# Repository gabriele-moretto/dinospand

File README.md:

# DinoSpand

The purpose of this board is to be mounted on a fertilizer spreader (an agricultural tool) to manage the drawer in which we load/unload the fertilizer.
While managing the tool, we'll see all the information in the cabin on the little OLED screen on the board, but also we will able to connect the device to our smartphone in order to managing some settings.

## Hardware

The microcontroller used is an ESP32-s3, which is useful for the right number of GPIO we need and for the bluetooth functions.

## Firmware

## [PCBWay](https://www.pcbway.com/) production
I had a great experience working with **PCBWay** through their sponsorship program. They supported my project by manufacturing and shipping a fully assembled PCB, which allowed me to turn my design into a real, working device.

**Key points:**
- PCB manufacturing
- High-quality fabrication and assembly
- Easy ordering process
- Fast production and shipping
- Reliable results

Many thanks to PCBWay for supporting this project!

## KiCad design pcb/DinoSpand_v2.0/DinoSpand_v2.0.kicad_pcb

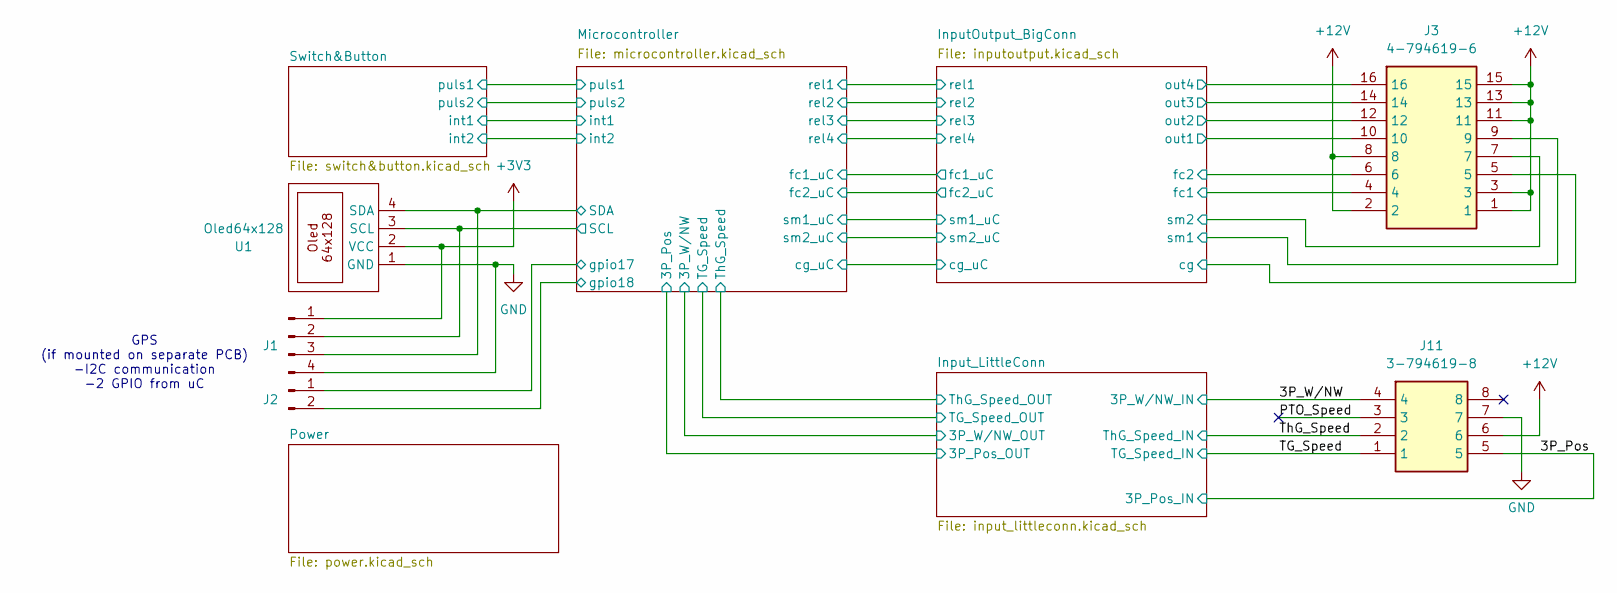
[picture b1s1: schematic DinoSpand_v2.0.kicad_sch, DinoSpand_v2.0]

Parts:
J1: Conn_01x04_Pin; PinHeader_1x04_P2.54mm_Vertical
J2: Conn_01x02_Pin; PinHeader_1x02_P2.54mm_Vertical
J3: 4-794619-6; 47946196; Mouser Part Number 571-4-794619-6
J11: 3-794619-8; 37946198; Mouser Part Number 571-3-794619-8
U1: Oled64x128; 128x64OLED

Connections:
+3V3: J1.1, U1.2 (VCC); also elsewhere on the board
+12V: J3.1, J3.2, J3.3, J3.8, J3.11, J3.13, J3.15, J11.6; also elsewhere on the board
/3P_Pos: J11.5; also elsewhere on the board
/3P_W/NW: J11.4; also elsewhere on the board
/InputOutput_BigConn/cg: J3.5; also elsewhere on the board
/InputOutput_BigConn/out1: J3.10; also elsewhere on the board
/InputOutput_BigConn/out2: J3.12; also elsewhere on the board
/InputOutput_BigConn/out3: J3.14; also elsewhere on the board
/InputOutput_BigConn/out4: J3.16; also elsewhere on the board
/InputOutput_BigConn/sm1: J3.9; also elsewhere on the board
/InputOutput_BigConn/sm2: J3.7; also elsewhere on the board
/Microcontroller/GPIO10: J3.4; also elsewhere on the board
/Microcontroller/GPIO11: J3.6; also elsewhere on the board
/Microcontroller/GPIO15: J1.3, U1.4 (SDA); also elsewhere on the board
/Microcontroller/GPIO16: J1.2, U1.3 (SCL); also elsewhere on the board
/Microcontroller/GPIO17: J2.1; also elsewhere on the board
/Microcontroller/GPIO18: J2.2; also elsewhere on the board
/PTO_Speed: J11.3
/TG_Speed: J11.1; also elsewhere on the board
/ThG_Speed: J11.2; also elsewhere on the board
GND: J1.4, J11.7, U1.1 (GND); also elsewhere on the board

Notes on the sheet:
GPS (if mounted on separate PCB) -I2C communication -2 GPIO from uC

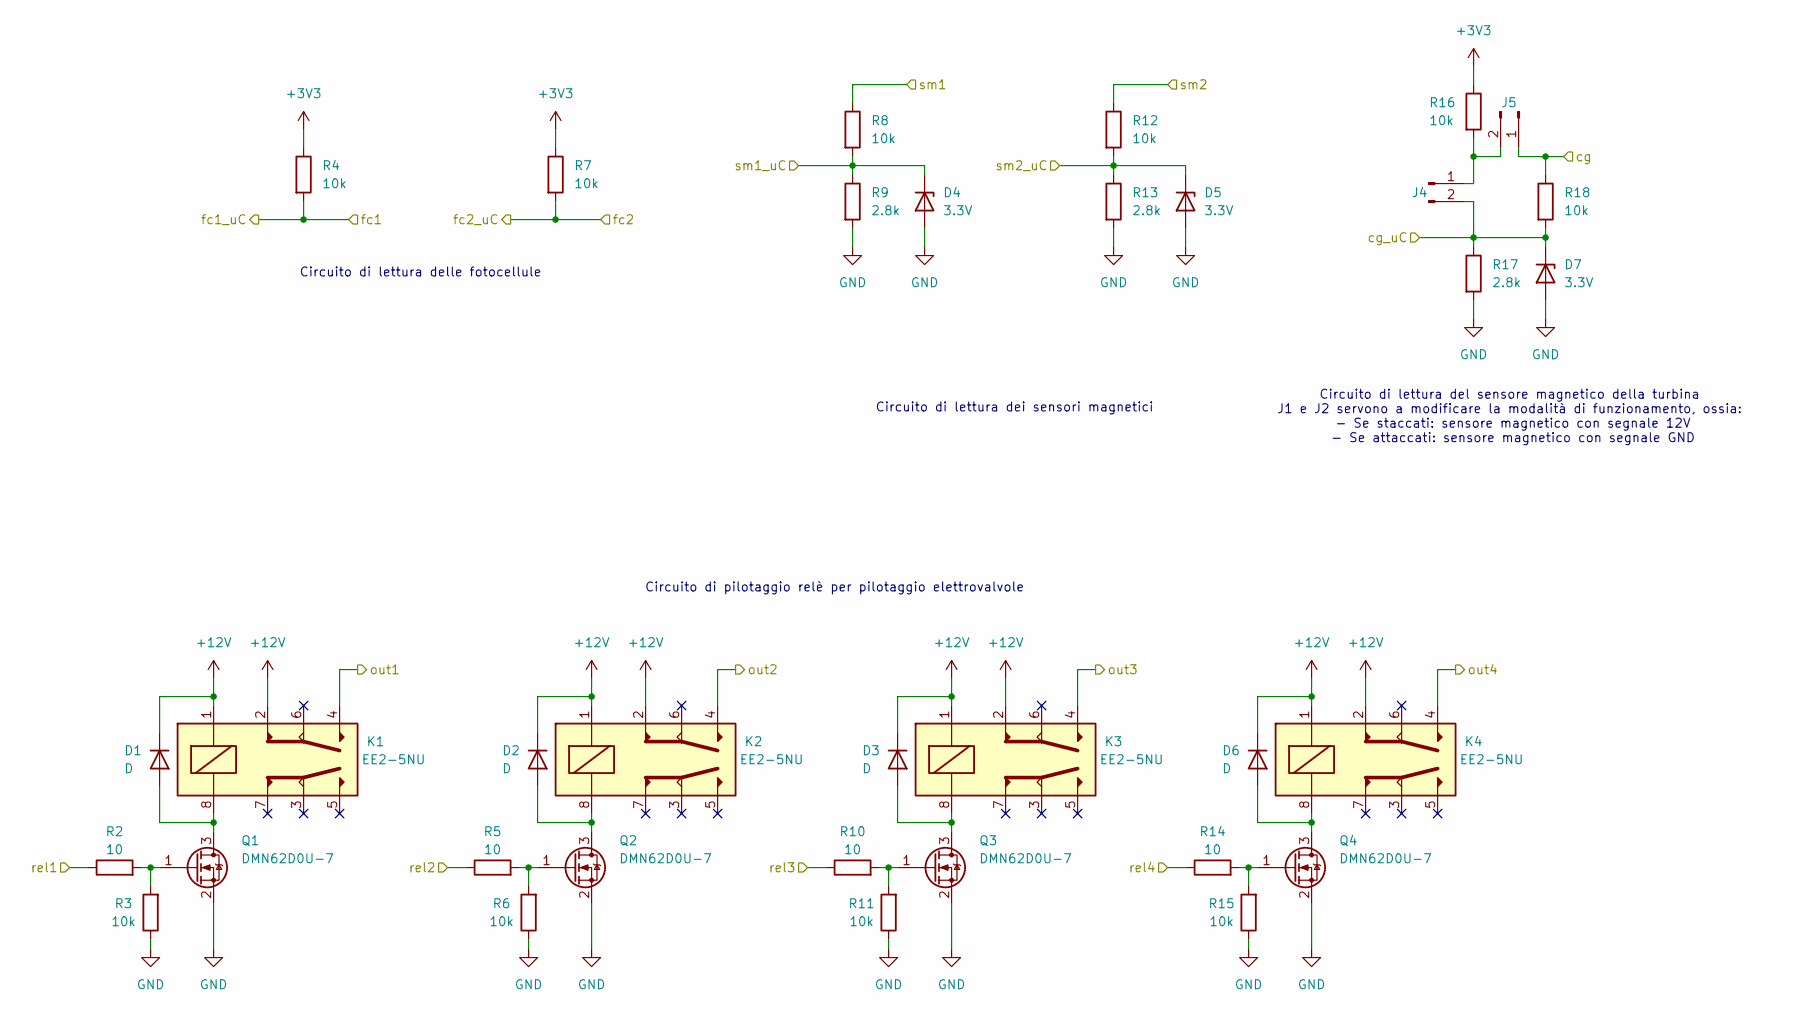
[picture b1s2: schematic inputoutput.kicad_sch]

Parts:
D1, D2, D3, D6: D; SODFL2512X90N
D4, D5, D7: 3.3V; SOD2512X110N
J4, J5: Conn_01x02_Pin; PinHeader_1x02_P2.54mm_Vertical
K1, K2, K3, K4: EE2-5NU; Mouser Part Number 80-EE2-5NU
Q1, Q2, Q3, Q4: DMN62D0U-7; SOT96P240X110-3N; Mouser Part Number 621-DMN62D0U-7
R2, R5, R10, R14: 10; R_0603_1608Metric
R3, R4, R6, R7, R8, R11, R12, R15, R16, R18: 10k; R_0603_1608Metric
R9, R13, R17: 2.8k; R_0603_1608Metric

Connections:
+3V3: R4.1, R7.1, R16.1; also elsewhere on the board
+12V: D1.1 (K), D2.1 (K), D3.1 (K), D6.1 (K), K1.1, K1.2, K2.1, K2.2, K3.1, K3.2, K4.1, K4.2; also elsewhere on the board
/InputOutput_BigConn/cg: J5.1, R18.1; also elsewhere on the board
/InputOutput_BigConn/out1: K1.4; also elsewhere on the board
/InputOutput_BigConn/out2: K2.4; also elsewhere on the board
/InputOutput_BigConn/out3: K3.4; also elsewhere on the board
/InputOutput_BigConn/out4: K4.4; also elsewhere on the board
/InputOutput_BigConn/sm1: R8.1; also elsewhere on the board
/InputOutput_BigConn/sm2: R12.1; also elsewhere on the board
/Microcontroller/GPIO10: R4.2; also elsewhere on the board
/Microcontroller/GPIO11: R7.2; also elsewhere on the board
/Microcontroller/GPIO12: D4.1 (K), R8.2, R9.1; also elsewhere on the board
/Microcontroller/GPIO13: D5.1 (K), R12.2, R13.1; also elsewhere on the board
/Microcontroller/GPIO14: D7.1 (K), J4.2, R17.1, R18.2; also elsewhere on the board
/Microcontroller/GPIO21: R2.1; also elsewhere on the board
/Microcontroller/GPIO37: R14.1; also elsewhere on the board
/Microcontroller/GPIO47: R5.1; also elsewhere on the board
/Microcontroller/GPIO48: R10.1; also elsewhere on the board
GND: D4.2 (A), D5.2 (A), D7.2 (A), Q1.2 (S), Q2.2 (S), Q3.2 (S), Q4.2 (S), R3.1, R6.1, R9.2, R11.1, R13.2, R15.1, R17.2; also elsewhere on the board
unnamed: D1.2 (A), K1.8, Q1.3 (D)
unnamed: D2.2 (A), K2.8, Q2.3 (D)
unnamed: D3.2 (A), K3.8, Q3.3 (D)
unnamed: D6.2 (A), K4.8, Q4.3 (D)
unnamed: J4.1, J5.2, R16.2
unnamed: Q1.1 (G), R2.2, R3.2
unnamed: Q2.1 (G), R5.2, R6.2
unnamed: Q3.1 (G), R10.2, R11.2
unnamed: Q4.1 (G), R14.2, R15.2

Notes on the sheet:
Circuito di pilotaggio relè per pilotaggio elettrovalvole
Circuito di lettura del sensore magnetico della turbina J1 e J2 servono a modificare la modalità di funzionamento, ossia: - Se staccati: sensore magnetico con segnale 12V - Se attaccati: sensore magnetico con segnale GND
Circuito di lettura dei sensori magnetici
Circuito di lettura delle fotocellule

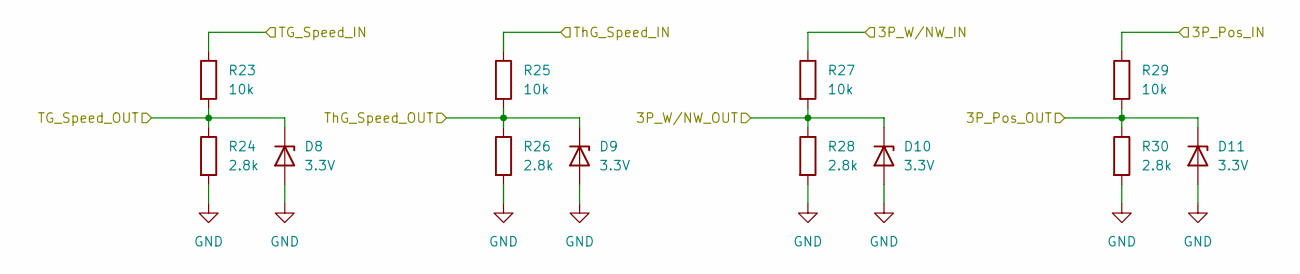
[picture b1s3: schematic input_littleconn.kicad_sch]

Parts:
D8, D9, D10, D11: 3.3V; SOD2512X110N
R23, R25, R27, R29: 10k; R_0603_1608Metric
R24, R26, R28, R30: 2.8k; R_0603_1608Metric

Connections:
/3P_Pos: R29.1; also elsewhere on the board
/3P_W/NW: R27.1; also elsewhere on the board
/Microcontroller/GPIO9: D10.1 (K), R27.2, R28.1; also elsewhere on the board
/Microcontroller/GPIO35: D9.1 (K), R25.2, R26.1; also elsewhere on the board
/Microcontroller/GPIO36: D8.1 (K), R23.2, R24.1; also elsewhere on the board
/Microcontroller/GPIO38: D11.1 (K), R29.2, R30.1; also elsewhere on the board
/TG_Speed: R23.1; also elsewhere on the board
/ThG_Speed: R25.1; also elsewhere on the board
GND: D8.2 (A), D9.2 (A), D10.2 (A), D11.2 (A), R24.2, R26.2, R28.2, R30.2; also elsewhere on the board

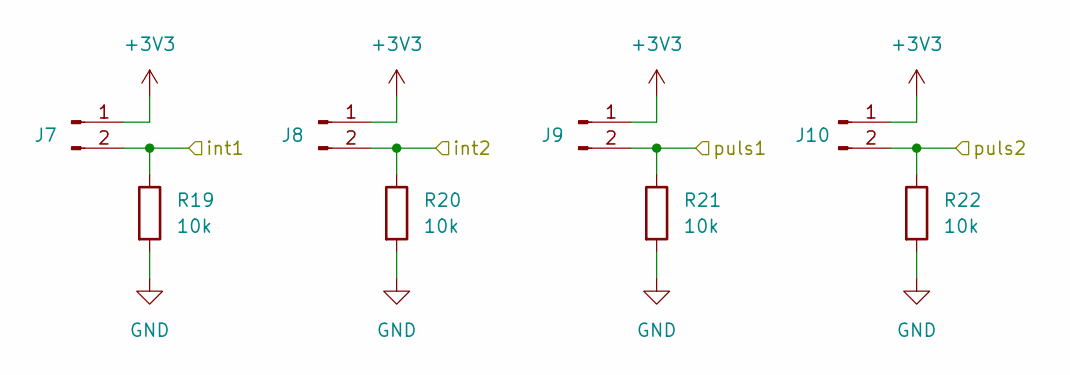
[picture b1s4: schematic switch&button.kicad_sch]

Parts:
J7, J8, J9, J10: Conn_01x02_Pin; PinHeader_1x02_P2.54mm_Vertical
R19, R20, R21, R22: 10k; R_0603_1608Metric

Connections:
+3V3: J7.1, J8.1, J9.1, J10.1; also elsewhere on the board
/Microcontroller/GPIO4: J7.2, R19.1; also elsewhere on the board
/Microcontroller/GPIO5: J8.2, R20.1; also elsewhere on the board
/Microcontroller/GPIO6: J9.2, R21.1; also elsewhere on the board
/Microcontroller/GPIO7: J10.2, R22.1; also elsewhere on the board
GND: R19.2, R20.2, R21.2, R22.2; also elsewhere on the board

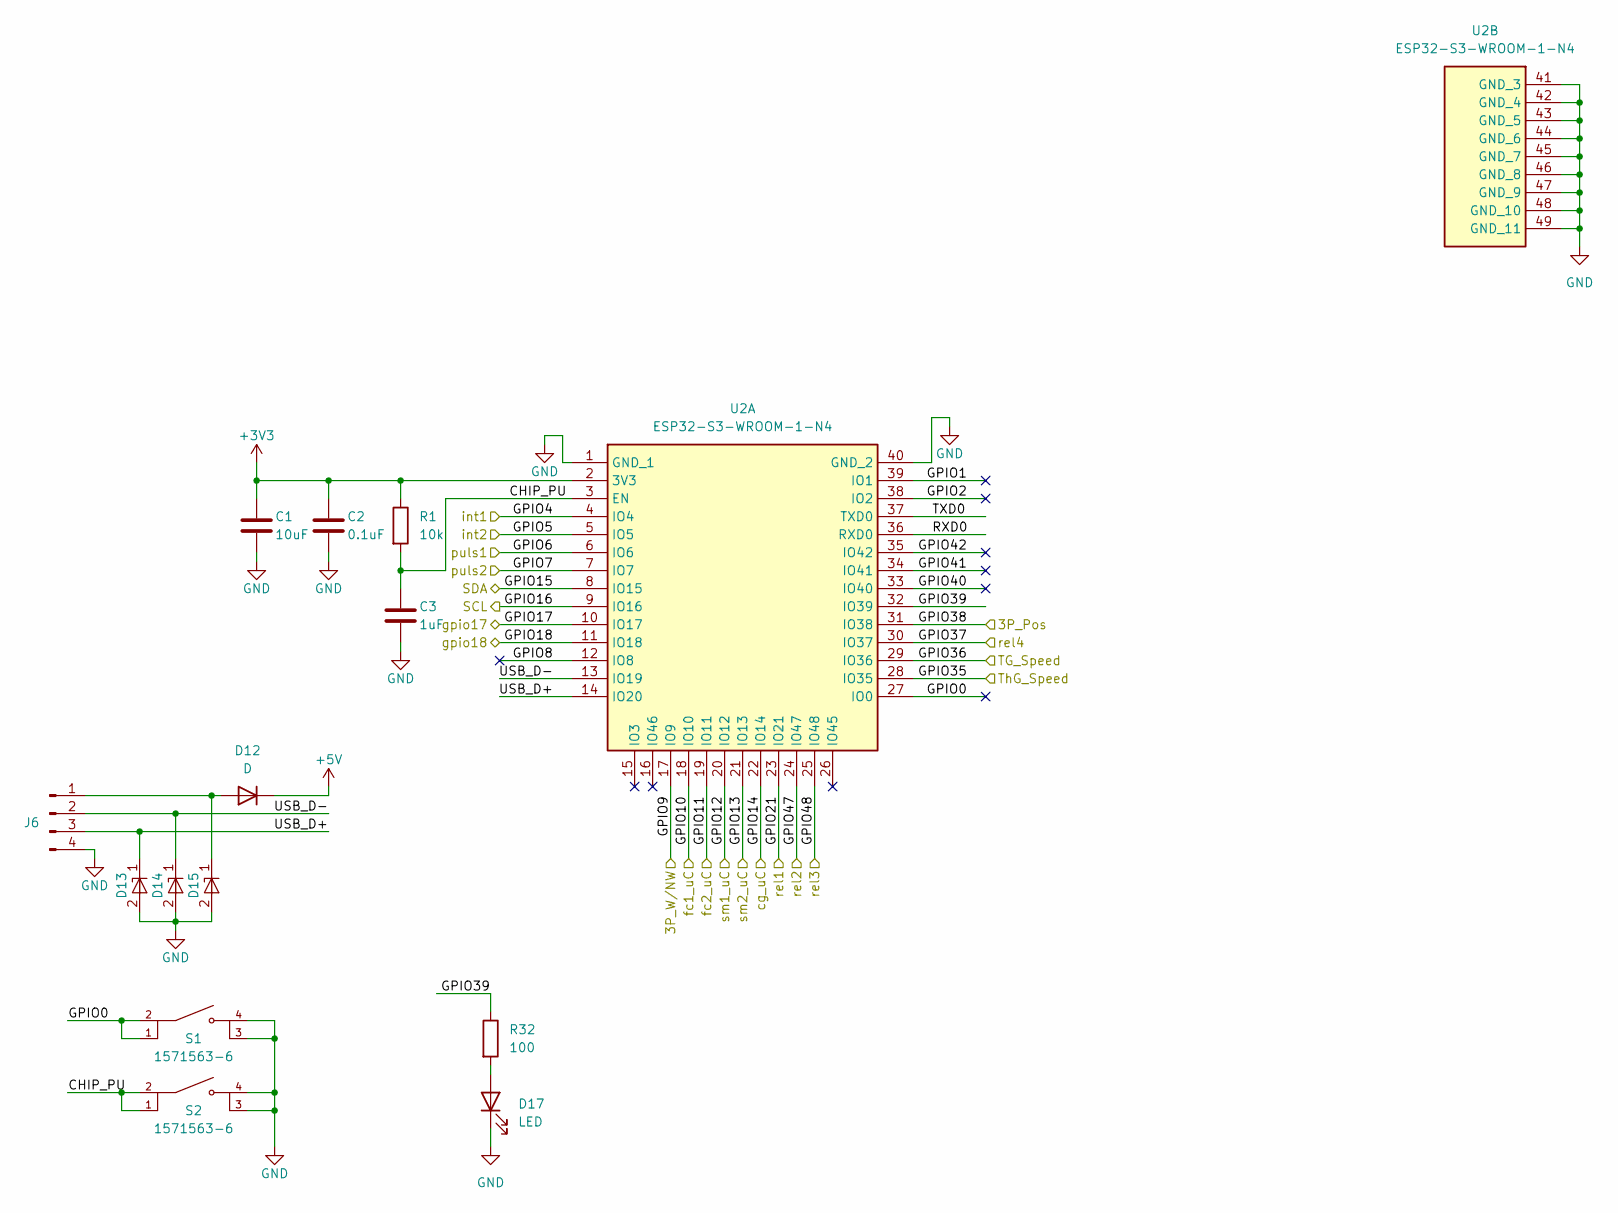
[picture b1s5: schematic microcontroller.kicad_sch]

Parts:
C1: 10uF; C_0603_1608Metric
C2: 0.1uF; C_0603_1608Metric
C3: 1uF; C_0603_1608Metric
D12: D; SODFL1608X70N
D13, D14, D15: SZESD5B5.0ST5G; SODFL1608X70N; Mouser Part Number 863-SZESD5B5.0ST5G
D17: LED; LED_D3.0mm
J6: Conn_01x04_Pin; PinHeader_1x04_P2.54mm_Vertical
R1: 10k; R_0603_1608Metric
R32: 100; R_0603_1608Metric
S1, S2: 1571563-6; SW_1571563-6; PARTREV V
U2: ESP32-S3-WROOM-1-N4; ESP32S3WROOM1N4; Mouser Part Number 356-ESP32-S3WROOM1N4

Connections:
+3V3: C1.1, C2.1, R1.1, U2.2 (3V3); also elsewhere on the board
+5V: D12.1 (K); also elsewhere on the board
/Microcontroller/CHIP_PU: C3.1, R1.2, S2.1, S2.2, U2.3 (EN)
/Microcontroller/GPIO0: S1.1, S1.2, U2.27 (IO0)
/Microcontroller/GPIO1: U2.39 (IO1)
/Microcontroller/GPIO2: U2.38 (IO2)
/Microcontroller/GPIO4: U2.4 (IO4); also elsewhere on the board
/Microcontroller/GPIO5: U2.5 (IO5); also elsewhere on the board
/Microcontroller/GPIO6: U2.6 (IO6); also elsewhere on the board
/Microcontroller/GPIO7: U2.7 (IO7); also elsewhere on the board
/Microcontroller/GPIO8: U2.12 (IO8)
/Microcontroller/GPIO9: U2.17 (IO9); also elsewhere on the board
/Microcontroller/GPIO10: U2.18 (IO10); also elsewhere on the board
/Microcontroller/GPIO11: U2.19 (IO11); also elsewhere on the board
/Microcontroller/GPIO12: U2.20 (IO12); also elsewhere on the board
/Microcontroller/GPIO13: U2.21 (IO13); also elsewhere on the board
/Microcontroller/GPIO14: U2.22 (IO14); also elsewhere on the board
/Microcontroller/GPIO15: U2.8 (IO15); also elsewhere on the board
/Microcontroller/GPIO16: U2.9 (IO16); also elsewhere on the board
/Microcontroller/GPIO17: U2.10 (IO17); also elsewhere on the board
/Microcontroller/GPIO18: U2.11 (IO18); also elsewhere on the board
/Microcontroller/GPIO21: U2.23 (IO21); also elsewhere on the board
/Microcontroller/GPIO35: U2.28 (IO35); also elsewhere on the board
/Microcontroller/GPIO36: U2.29 (IO36); also elsewhere on the board
/Microcontroller/GPIO37: U2.30 (IO37); also elsewhere on the board
/Microcontroller/GPIO38: U2.31 (IO38); also elsewhere on the board
/Microcontroller/GPIO39: R32.1, U2.32 (IO39)
/Microcontroller/GPIO40: U2.33 (IO40)
/Microcontroller/GPIO41: U2.34 (IO41)
/Microcontroller/GPIO42: U2.35 (IO42)
/Microcontroller/GPIO47: U2.24 (IO47); also elsewhere on the board
/Microcontroller/GPIO48: U2.25 (IO48); also elsewhere on the board
/Microcontroller/RXD0: U2.36 (RXD0)
/Microcontroller/TXD0: U2.37 (TXD0)
/Microcontroller/USB_D+: D13.1 (K1), J6.3, U2.14 (IO20)
/Microcontroller/USB_D-: D14.1 (K1), J6.2, U2.13 (IO19)
GND: C1.2, C2.2, C3.2, D13.2 (A), D14.2 (A), D15.2 (A), D17.1 (K), J6.4, S1.3, S1.4, S2.3, S2.4, U2.1 (GND_1), U2.40 (GND_2), U2.41 (GND_3), U2.42 (GND_4), U2.43 (GND_5), U2.44 (GND_6), U2.45 (GND_7), U2.46 (GND_8), U2.47 (GND_9), U2.48 (GND_10), U2.49 (GND_11); also elsewhere on the board
unnamed: D12.2 (A), D15.1 (K1), J6.1
unnamed: D17.2 (A), R32.2

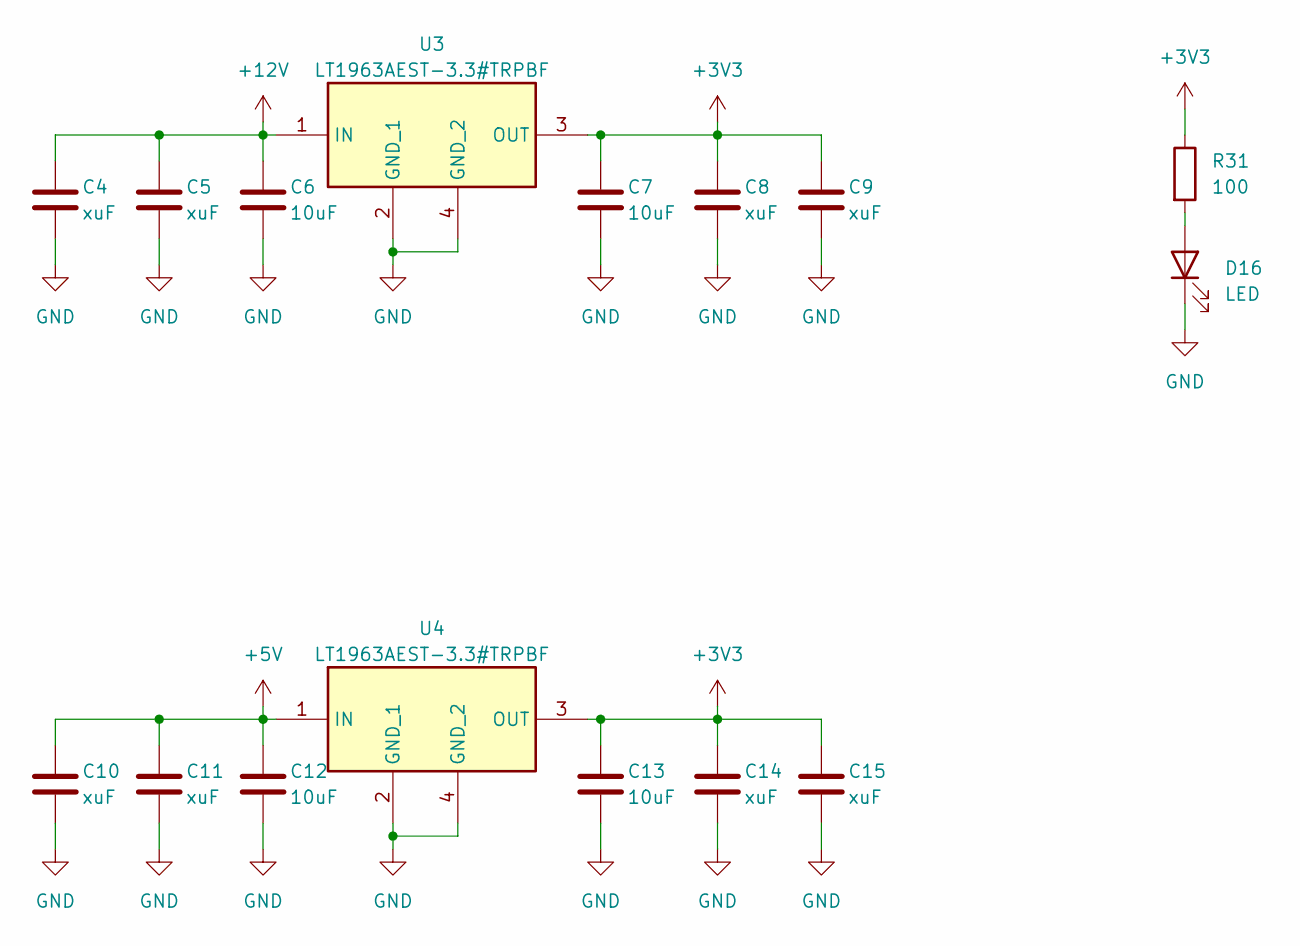
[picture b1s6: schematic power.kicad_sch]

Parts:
C4, C9, C10: xuF; CP_Radial_D4.0mm_P2.00mm
C5, C8, C11, C14, C15: xuF; C_0603_1608Metric
C6, C7, C12, C13: 10uF; C_0603_1608Metric
D16: LED; LED_0603_1608Metric
R31: 100; R_0603_1608Metric
U3, U4: LT1963AEST-3.3#TRPBF; SOT230P700X180-4N; Mouser Part Number 584-1963AEST-3.3TPF

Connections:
+3V3: C7.1, C8.1, C9.1, C13.1, C14.1, C15.1, R31.1, U3.3 (OUT), U4.3 (OUT); also elsewhere on the board
+5V: C10.1, C11.1, C12.1, U4.1 (IN); also elsewhere on the board
+12V: C4.1, C5.1, C6.1, U3.1 (IN); also elsewhere on the board
GND: C4.2, C5.2, C6.2, C7.2, C8.2, C9.2, C10.2, C11.2, C12.2, C13.2, C14.2, C15.2, D16.1 (K), U3.2 (GND_1), U3.4 (GND_2), U4.2 (GND_1), U4.4 (GND_2); also elsewhere on the board
unnamed: D16.2 (A), R31.2

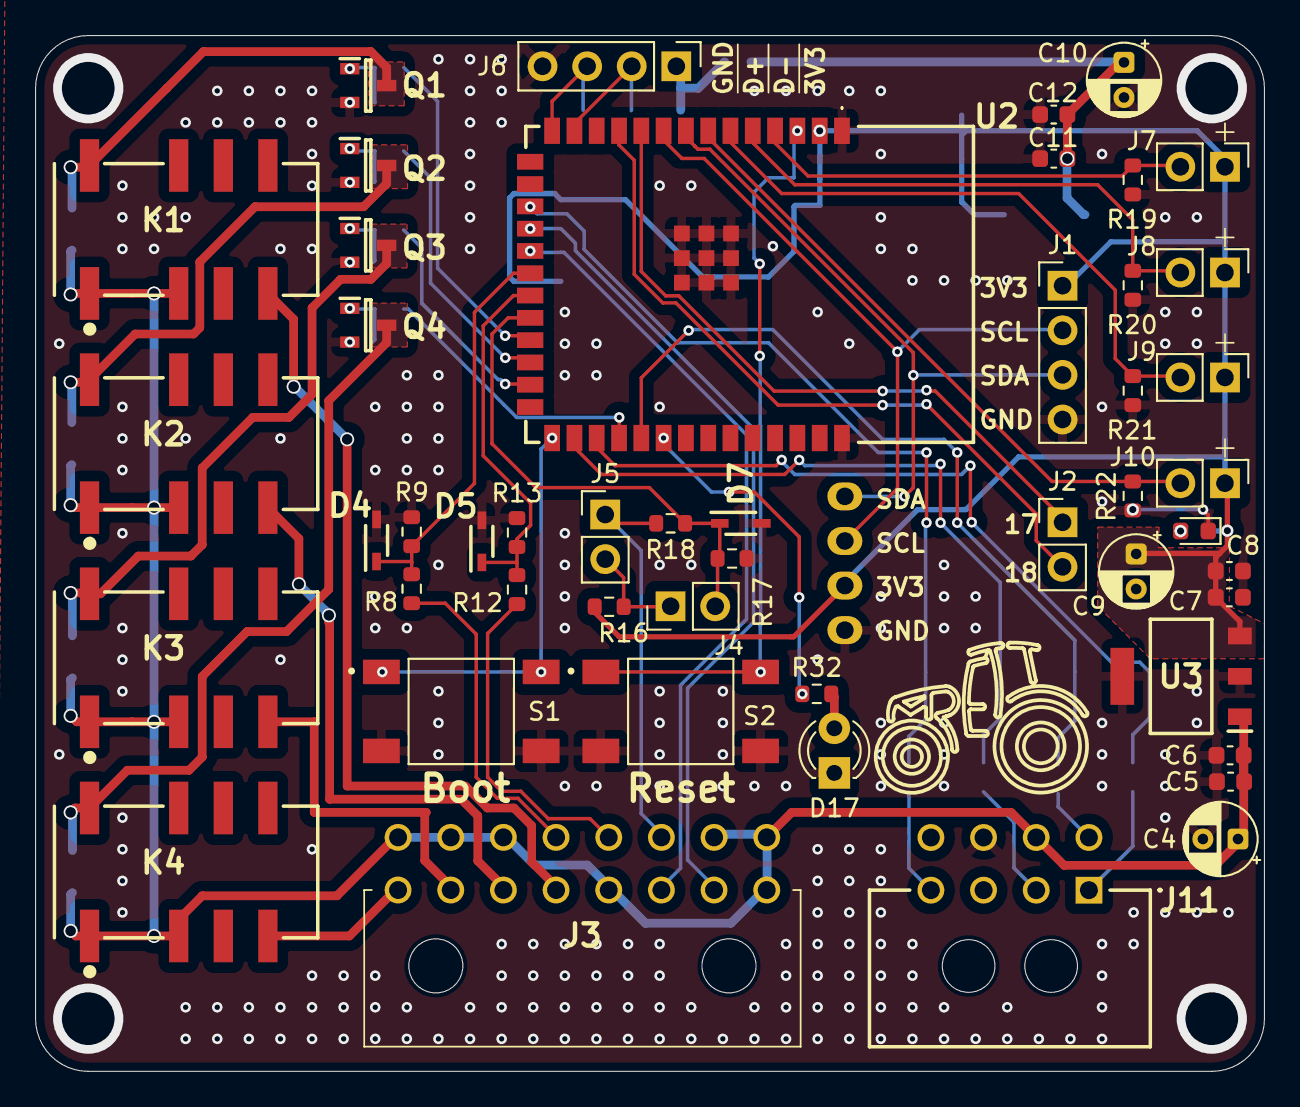
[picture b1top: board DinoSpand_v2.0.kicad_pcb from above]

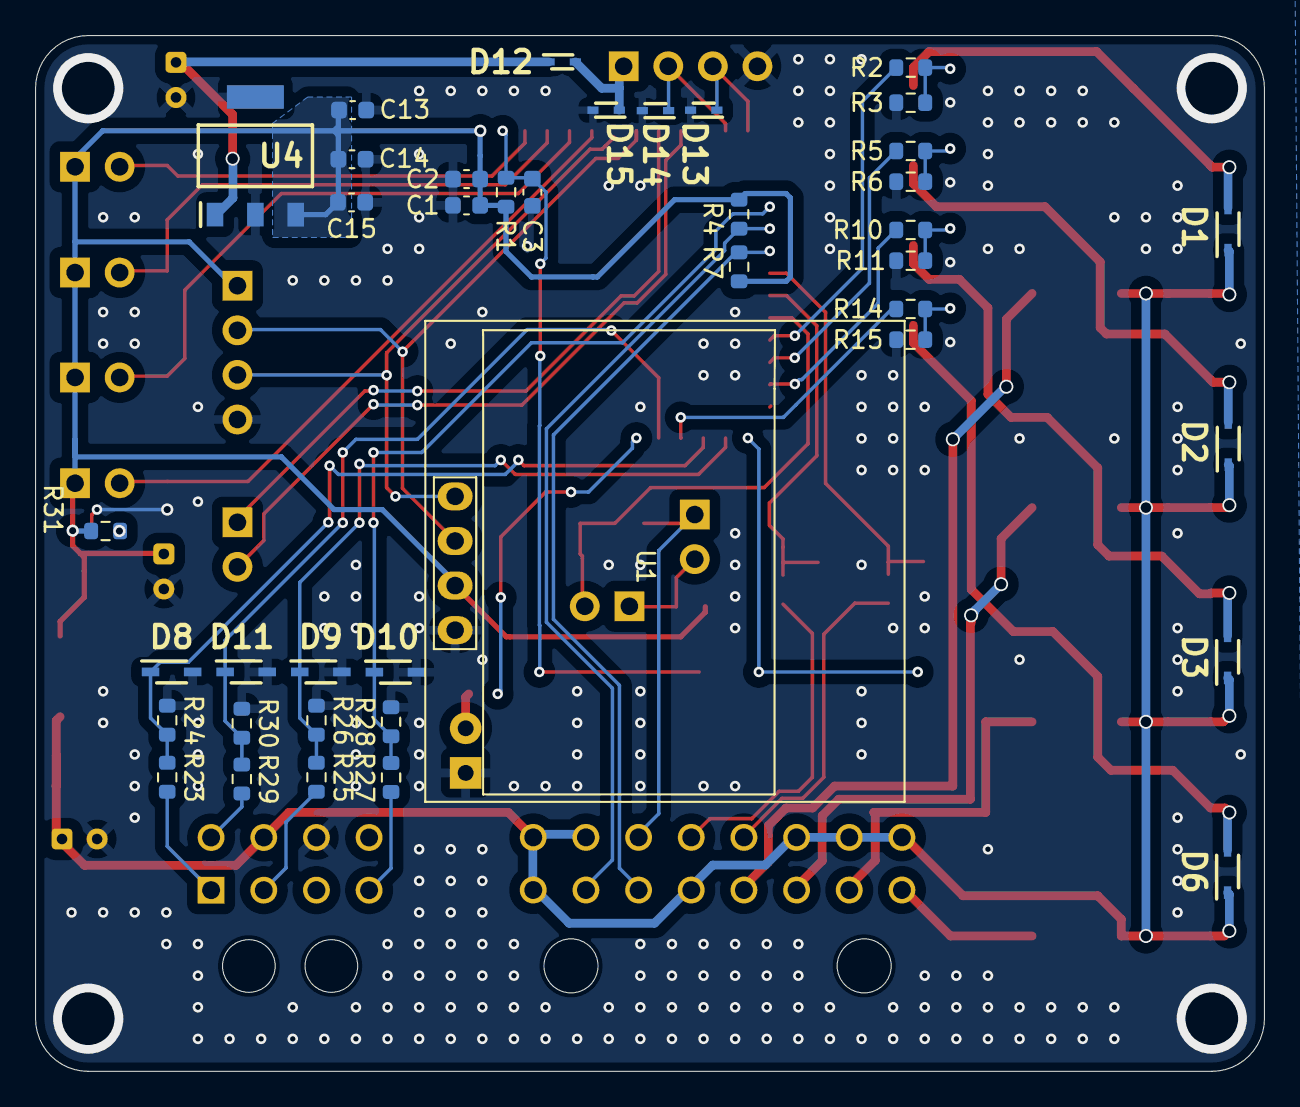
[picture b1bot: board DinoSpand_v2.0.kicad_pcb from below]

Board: 2 copper layers, 70.0 x 59.0 mm, 89 parts (40 on the bottom side), 53 nets.

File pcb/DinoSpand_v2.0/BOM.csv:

Id;Designator;Footprint;Quantity;Designation;Supplier and ref
1;D7,D5,D4,D11,D8,D10,D9;SOD2512X110N;7;3.3V;
2;C7,C12,C6,C13,C1;C_0603_1608Metric;5;10uF;
3;C4,C10,C9;CP_Radial_D4.0mm_P2.00mm;3;xuF;
4;Q2,Q4,Q1,Q3;SOT96P240X110-3N;4;DMN62D0U-7;
5;R21,R16,R22,R8,R19,R20,R18,R12,R1,R6,R11,R29,R4,R15,R3,R25,R7,R27,R23;R_0603_1608Metric;19;10k;
6;S1,S2;SW_1571563-6;2;1571563-6;
7;C8,C11,C5,C14,C15;C_0603_1608Metric;5;xuF;
8;K3,K1,K2,K4;EE2-5NU;4;EE2-5NU;
9;U3,U4;SOT230P700X180-4N;2;LT1963AEST-3.3#TRPBF;
10;J11;37946198;1;3-794619-8;
11;R32,R31;R_0603_1608Metric;2;100;
12;D16;LED_0603_1608Metric;1;LED;
13;D17;LED_D3.0mm;1;LED;
14;U2;ESP32S3WROOM1N4;1;ESP32-S3-WROOM-1-N4;
15;R9,R13,R17,R30,R26,R24,R28;R_0603_1608Metric;7;2.8k;
16;J3;47946196;1;4-794619-6;
17;R10,R14,R2,R5;R_0603_1608Metric;4;10;
18;D15,D14,D13;SODFL1608X70N;3;SZESD5B5.0ST5G;
19;C2;C_0603_1608Metric;1;0.1uF;
20;D6,D3,D1,D2;SODFL2512X90N;4;D;
21;C3;C_0603_1608Metric;1;1uF;
22;D12;SODFL1608X70N;1;D;
23;U1;128x64OLED;1;Oled64x128;

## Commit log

2025-12-01 general_update
2025-12-06 pcbs update
2025-12-06 readme update
2025-12-27 pcbs final update
2025-12-27 remove git ignore
2026-02-27 Enhance README with PCBWay production details
    Added a section about PCBWay production experience and firmware.
2026-03-03 Link to PCBWay
